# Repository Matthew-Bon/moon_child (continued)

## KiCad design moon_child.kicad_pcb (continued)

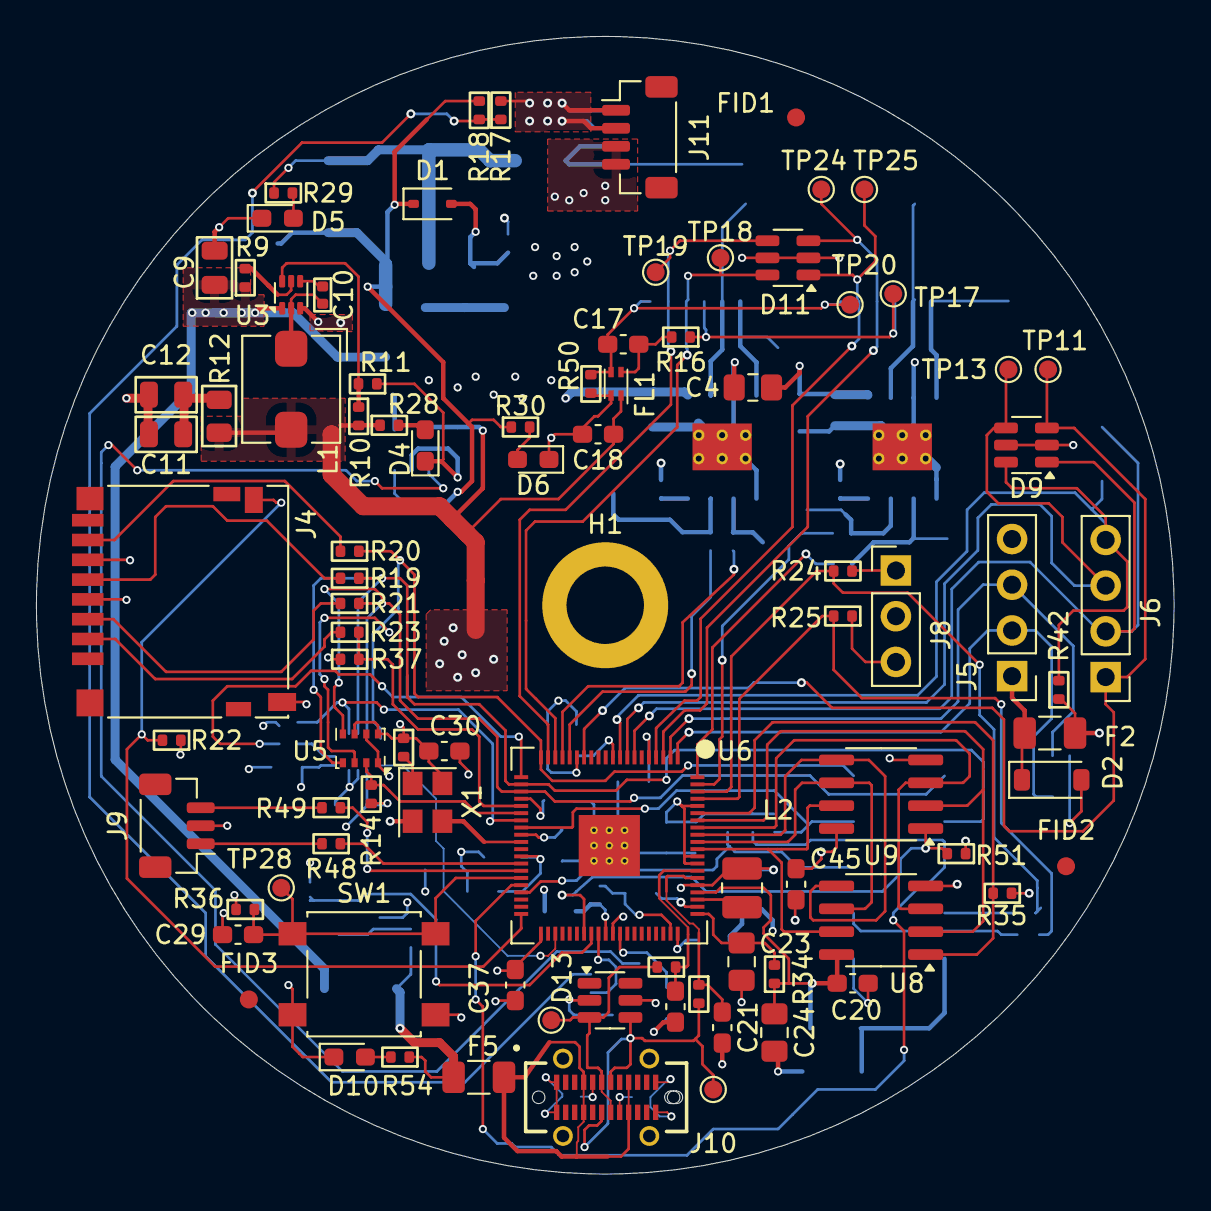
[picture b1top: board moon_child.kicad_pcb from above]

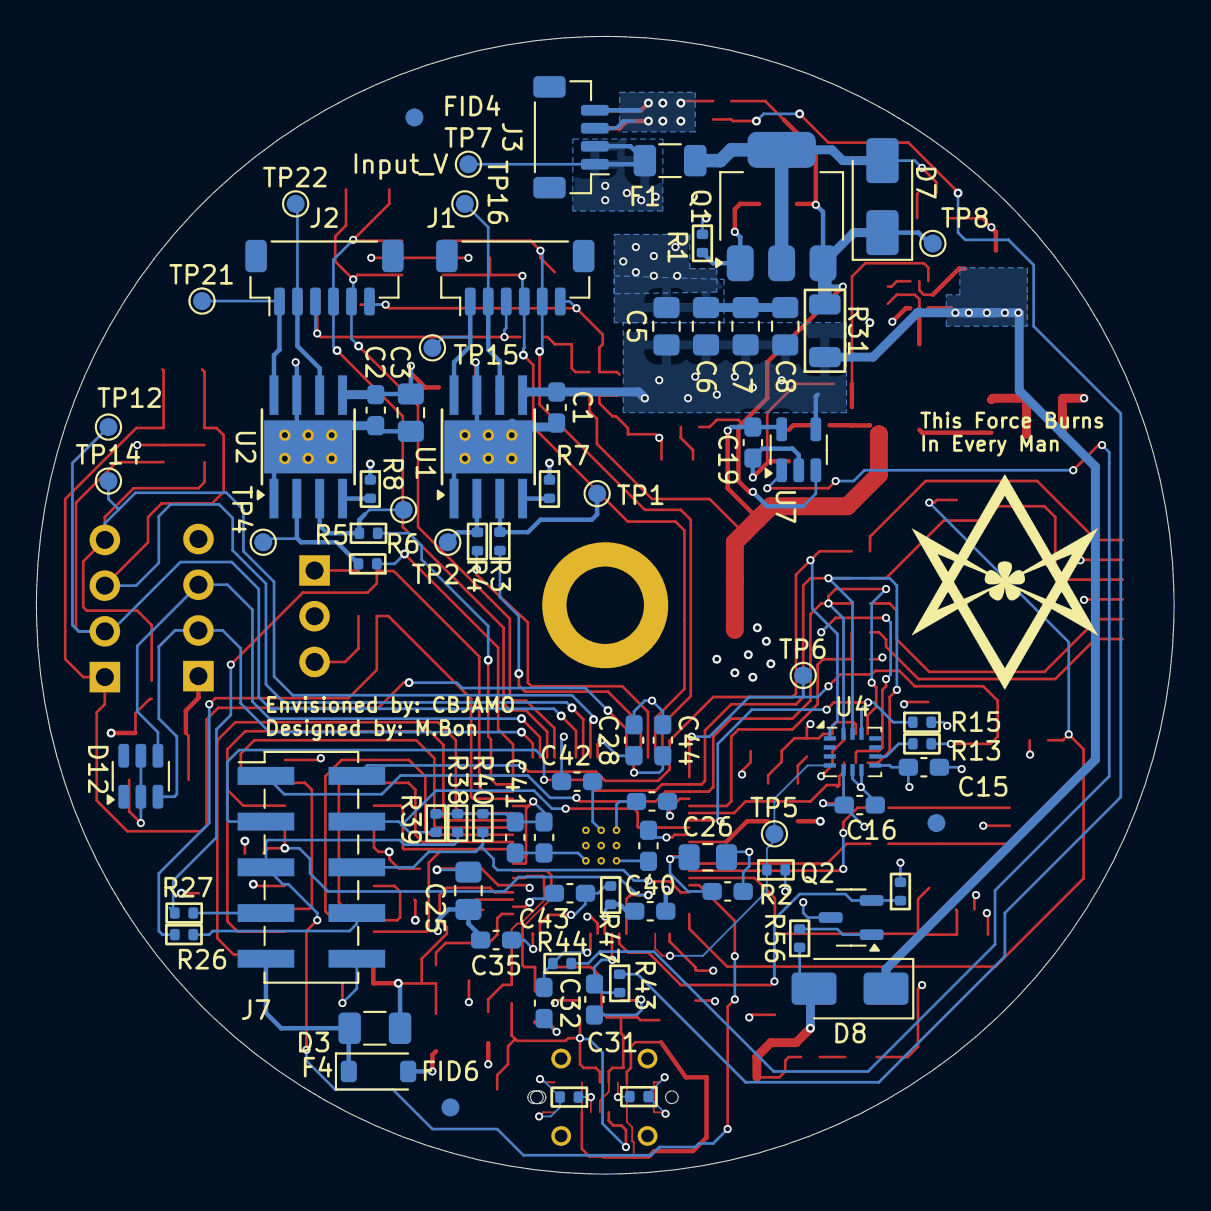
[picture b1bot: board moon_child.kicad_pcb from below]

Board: 4 copper layers, 63.2 x 63.2 mm, 171 parts (81 on the bottom side), 100 nets.

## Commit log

2024-09-02 Added connectors
    Added GPS and SD card connections
2024-09-02 Delete LICENSE
    Removed MIT license in order to swap to GPL 3.0
2024-09-02 Create LICENSE
    Added GPL 3 License since I plan to incorporate some libraries that use it.
2024-09-03 Updated schematics
    Added the input current sense, expansion header and various test points.
2024-09-08 Added RPI stuff
    Added power passives and usb passives
2024-09-08 Setup top sheet
    Added TVS diodes, updated top sheet, misc label fixes
2024-09-08 Updated Raspi Sheet
    Added hierarchical labels and misc additions.
2024-11-24 Updated MCU pinout
    Added bypass caps and started assigning pinouts.
2024-11-24 Finnished pinouts
    pending input from firmware
2024-11-24 Updated sheet to sheet pinout
    Updated pinouts and cleared ERCs
2024-12-01 started layout
    Preliminary footprint selection
2024-12-01 footprint cleanup
    switched to 0402 resistors, updated connectors, etc...
2024-12-01 lock file fix
    Removed .lck files and updated the git ignore
2024-12-01 Added USB C Connector
    Added usb C connector, consolidated ESD parts, cleaned up footprint selection.
2024-12-02 Updated layout
    Added ground fills, updated stackup, added notes.
2024-12-29 Swapped USB to Vert
    Changed USB-C connector from horizontal to vertical
2024-12-29 Swapped motor polarity
    Swapped motor polarity for easier routing + other component positioning.
2024-12-29 Updated routing
2025-01-20 Layout updates
    Added 3v3 switcher layout + extras
2025-01-20 QSPI routing
    Added pretty sub-optimal qspi routing
2025-01-21 GPS layout
    Routed gps and motor control connections
2025-01-25 Moved passives
    Lots passive routing
2025-01-25 Distributed caps
    Remembered to add decoupling caps
2025-01-25 imu routing
    updates to imu routes
2025-01-25 USB routing
    Updated usb routing
2025-03-16 Updates
    Routing updates, placed expansion connector.
2025-03-16 Removed auto save
2025-03-16 more routing updates
2025-04-20 layout updates
    Updated encoder, esd and other layouts
2025-05-17 Layout updates
    testpoints, usb power, etc.
2025-05-17 layout updates
    removes ADC 2 and ADC 3 connections for space reasons
2025-05-17 layout updates
    SPI routes
2025-05-17 Routing updates
    All nets connected, still need to clear DRCS and fix silks
2025-07-06 silkscreen cleanup
    Cleaned up silks
2025-08-16 silk fixes
2025-09-01 CBjamo updats
    Added J11 to accommodate batteries on both sides and changed pinout of J8 to have ground in the middle.
2025-09-01 swapped J8 pinout
2025-09-01 silk cleanup
    Updated PSRAM value to use a flash PN, Updated 0402 footprints to give more room between pads and silkscreen. cleaned up overlaps.
2025-09-01 More silk fixes
    More silk fixes
2025-09-13 layout cleanup
    increased some trace spaces for manufacturability. Cleaned up drc by ignoring pad rule.
2025-09-13 Bom updates
2025-09-13 Launch day
    Completed BOM, added silk art
2025-09-13 zip file update
